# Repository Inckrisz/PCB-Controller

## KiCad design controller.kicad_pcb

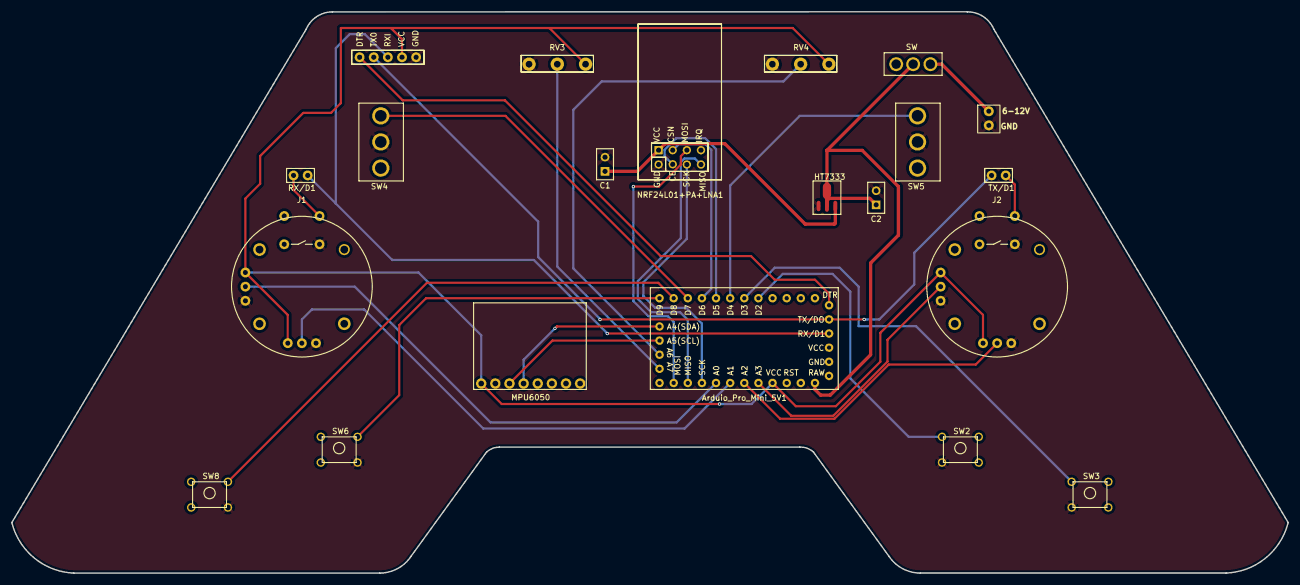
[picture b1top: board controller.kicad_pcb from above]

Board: 4 copper layers, 229.5 x 100.9 mm, 21 parts (0 on the bottom side), 29 nets.

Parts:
6-12V1: 6-12V
Arduio_Pro_Mini_5V1: ARDUINO
C1, C2: C
DTRTXORXIVCCGND1: MAIN_PINS
HT7333: HT7333
Joystick1, Joystick2: JOYSTICK
MPU6050: MPU6050
NRF24L01+PA+LNA1: NRF24L01
RV3, RV4: R_Potentiometer; POTENTIOMETER
RX/D1: RXD1
SW2, SW3, SW6, SW8: SW_Push_Dual; BTN
SW4, SW5: SW_SPDT; TOGGLE_SWITCH
SW7: SW_SPDT; SLIDING_SWITCH
TX/D1: TXD0

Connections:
3,3V: C1.2, HT7333.4 (VOUT), NRF24L01+PA+LNA1.1 (VCC)
6-12V: 6-12V1.3 (6-12V), SW7.1 (A)
CE: Arduio_Pro_Mini_5V1.5 (D5), NRF24L01+PA+LNA1.4 (CE)
CSN: Arduio_Pro_Mini_5V1.6 (D6), NRF24L01+PA+LNA1.3 (CSN)
DTR: Arduio_Pro_Mini_5V1.34 (DTR), DTRTXORXIVCCGND1.1 (DTR)
GND: 6-12V1.4 (GNDO), C1.1, C2.1, DTRTXORXIVCCGND1.5 (GND), HT7333.2 (GND), Joystick1.3 (GND), Joystick1.6 (GND), Joystick1.8 (GND), Joystick2.3 (GND), Joystick2.6 (GND), Joystick2.8 (GND), MPU6050.2 (GND), NRF24L01+PA+LNA1.2 (GND), RV3.1, RV4.1, SW2.3, SW3.3, SW4.2 (B), SW5.2 (B), SW6.4, SW8.4
MISO: Arduio_Pro_Mini_5V1.12 (D12), NRF24L01+PA+LNA1.8 (MISO)
MOSI: Arduio_Pro_Mini_5V1.11 (D11), NRF24L01+PA+LNA1.5 (MOSI)
unnamed: Arduio_Pro_Mini_5V1.35 (A5), Joystick2.5 (VOUT)
unnamed: Arduio_Pro_Mini_5V1.14 (A1), Joystick2.2 (VOUT)
unnamed: Arduio_Pro_Mini_5V1.15 (A2), Joystick1.2 (VOUT)
unnamed: Arduio_Pro_Mini_5V1.16 (A3), Joystick1.5 (VOUT)
unnamed: Arduio_Pro_Mini_5V1.25 (A4), MPU6050.4 (SDA)
unnamed: Arduio_Pro_Mini_5V1.26 (A5), MPU6050.3 (SCL)
unnamed: Arduio_Pro_Mini_5V1.27 (A6), RV4.2
unnamed: Arduio_Pro_Mini_5V1.28 (A7), RV3.2
unnamed: Arduio_Pro_Mini_5V1.2 (D2), SW2.1
unnamed: Arduio_Pro_Mini_5V1.3 (D3), SW3.1
unnamed: Arduio_Pro_Mini_5V1.4 (D4), SW5.3 (C)
unnamed: Arduio_Pro_Mini_5V1.7 (D7), SW4.3 (C)
unnamed: Arduio_Pro_Mini_5V1.8 (D8), SW8.2
unnamed: Arduio_Pro_Mini_5V1.9 (D9), SW6.2
unnamed: Joystick2.9 (DOUT), RX/D1.1 (RX)
unnamed: Joystick1.9 (DOUT), TX/D1.1 (TX)
RXI: Arduio_Pro_Mini_5V1.30 (RXI), DTRTXORXIVCCGND1.3 (RXI), RX/D1.2 (D1)
SCK: Arduio_Pro_Mini_5V1.13 (D13), NRF24L01+PA+LNA1.6 (SCK)
TX0: Arduio_Pro_Mini_5V1.29 (TXO), DTRTXORXIVCCGND1.2 (TXO), TX/D1.2 (D0)
VCC: Arduio_Pro_Mini_5V1.17 (VCC), DTRTXORXIVCCGND1.4 (VCC), Joystick1.1 (VCC), Joystick1.4 (VCC), Joystick2.1 (VCC), Joystick2.4 (VCC), MPU6050.1 (VCC), RV3.3, RV4.3
VIN: Arduio_Pro_Mini_5V1.20 (RAW), C2.2, HT7333.1 (VIN), HT7333.3 (VIN), SW7.2 (B)
